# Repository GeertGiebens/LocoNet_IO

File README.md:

# LocoNet_IO

This LocoNet project has moved to this link: [DIY LocoNet S88 DCC](https://github.com/GeertGiebens/DIY_LocoNet_S88_DCC/)

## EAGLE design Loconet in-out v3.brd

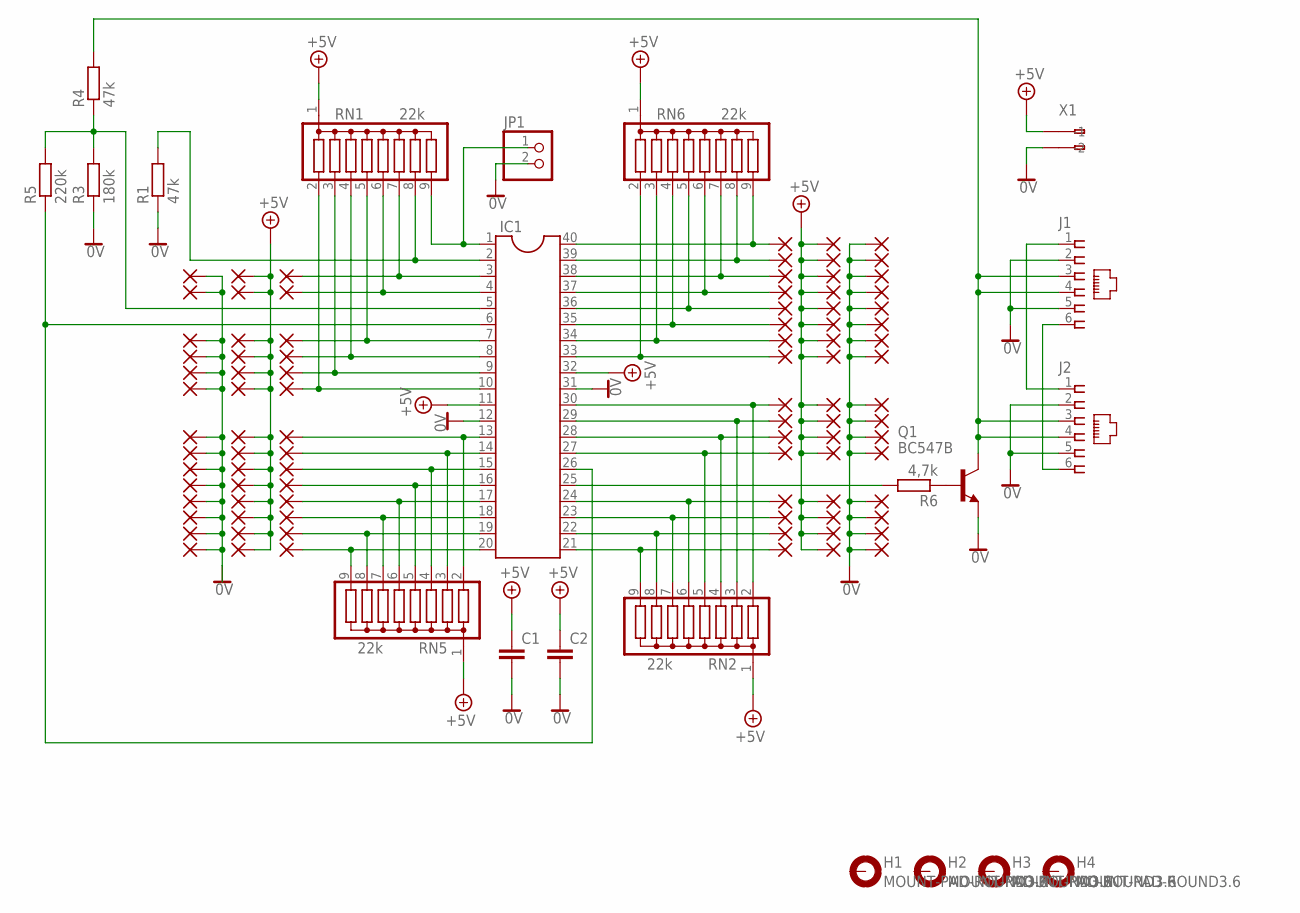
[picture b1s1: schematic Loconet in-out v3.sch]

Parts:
0, 2, 3, 4, 5, 6, 7, 8, 9, 10, 11, 12, 13, 14, 15, 16, 17, 18, 19, 20, 21, 22, 23, 24, 25, 26, 27, 28, 29, 30: 2,15/1,0
1: 1; 2,15/1,0
C1, C2: C-EU025-024X044; C025-024X044
H1, H2, H3, H4: MOUNT-PAD-ROUND3.6; 3,6-PAD
IC1: DIL40
J1, J2: 520250-3
JP1: PINHD-1X2; 1X02
PAD1, PAD2, PAD3, PAD4, PAD5, PAD6, PAD7, PAD8, PAD9, PAD10, PAD11, PAD12, PAD13, PAD14, PAD15, PAD16, PAD17, PAD18, PAD19, PAD20, PAD21, PAD22, PAD23, PAD24, PAD25, PAD26, PAD27, PAD28, PAD29, PAD30, PAD33, PAD35, PAD37, PAD39, PAD41, PAD43, PAD52, PAD53, PAD54, PAD55, PAD56, PAD57, PAD58, PAD59, PAD60, PAD61, PAD62, PAD63, PAD64, PAD65, PAD66, PAD67, PAD68, PAD69, PAD70, PAD71, PAD72, PAD73, PAD74: 2,15/1,0
Q1: BC547B; TO92
R1, R4: 47k; 0204/7
R3: 180k; 0204/7
R5: 220k; 0204/7
R6: 4,7k; 0204/7
RN1, RN2, RN5, RN6: 22k; SIL9
X1: 233-102

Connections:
+5V: 0.1, C1.1, C2.1, IC1.11, IC1.32, PAD33.1, PAD35.1, PAD37.1, PAD39.1, PAD41.1, PAD43.1, PAD52.1, PAD53.1, PAD54.1, PAD55.1, PAD56.1, PAD57.1, PAD58.1, PAD59.1, PAD60.1, PAD61.1, PAD62.1, PAD63.1, PAD64.1, PAD65.1, PAD66.1, PAD67.1, PAD68.1, PAD69.1, PAD70.1, PAD71.1, PAD72.1, PAD73.1, PAD74.1, RN1.1, RN2.1, RN5.1, RN6.1, X1.A1 (-1)
LN_RECEIVER: IC1.6, IC1.26, R5.1
LOCONET: J1.3, J1.4, J2.3, J2.4, Q1.3 (C), R4.2
unnamed: IC1.2, R1.2, RN1.8
unnamed: IC1.5, R3.2, R4.1, R5.2
unnamed: IC1.23, PAD20.1, RN2.7
unnamed: Q1.2 (B), R6.1
unnamed: J1.1, J2.1
unnamed: IC1.1, JP1.1, RN1.9
unnamed: IC1.40, PAD7.1, RN6.9
unnamed: J1.6, J2.6
unnamed: IC1.39, PAD8.1, RN6.8
unnamed: IC1.3, PAD1.1, RN1.7
unnamed: IC1.4, PAD2.1, RN1.6
unnamed: IC1.10, PAD6.1, RN1.2
unnamed: IC1.9, PAD5.1, RN1.3
unnamed: IC1.8, PAD4.1, RN1.4
unnamed: IC1.7, PAD3.1, RN1.5
unnamed: IC1.33, PAD14.1, RN6.2
unnamed: IC1.34, PAD13.1, RN6.3
unnamed: IC1.35, PAD12.1, RN6.4
unnamed: IC1.36, PAD11.1, RN6.5
unnamed: IC1.37, PAD10.1, RN6.6
unnamed: IC1.38, PAD9.1, RN6.7
unnamed: IC1.21, PAD22.1, RN2.9
unnamed: IC1.22, PAD21.1, RN2.8
unnamed: IC1.24, PAD19.1, RN2.6
unnamed: IC1.27, PAD18.1, RN2.5
unnamed: IC1.28, PAD17.1, RN2.4
unnamed: IC1.29, PAD16.1, RN2.3
unnamed: IC1.30, PAD15.1, RN2.2
unnamed: IC1.20, PAD23.1, RN5.9
unnamed: IC1.19, PAD24.1, RN5.8
unnamed: IC1.18, PAD25.1, RN5.7
unnamed: IC1.17, PAD26.1, RN5.6
unnamed: IC1.16, PAD27.1, RN5.5
unnamed: IC1.15, PAD28.1, RN5.4
unnamed: IC1.14, PAD29.1, RN5.3
unnamed: IC1.13, PAD30.1, RN5.2
unnamed: IC1.25, R6.2
unnamed: 1.1, 2.1, 3.1, 4.1, 5.1, 6.1, 7.1, 8.1, 9.1, 10.1, 11.1, 12.1, 13.1, 14.1, 15.1, 16.1, 17.1, 18.1, 19.1, 20.1, 21.1, 22.1, 23.1, 24.1, 25.1, 26.1, 27.1, 28.1, 29.1, 30.1, C1.2, C2.2, IC1.12, IC1.31, J1.2, J1.5, J2.2, J2.5, JP1.2, Q1.1 (E), R1.1, R3.1, X1.A2 (-2)

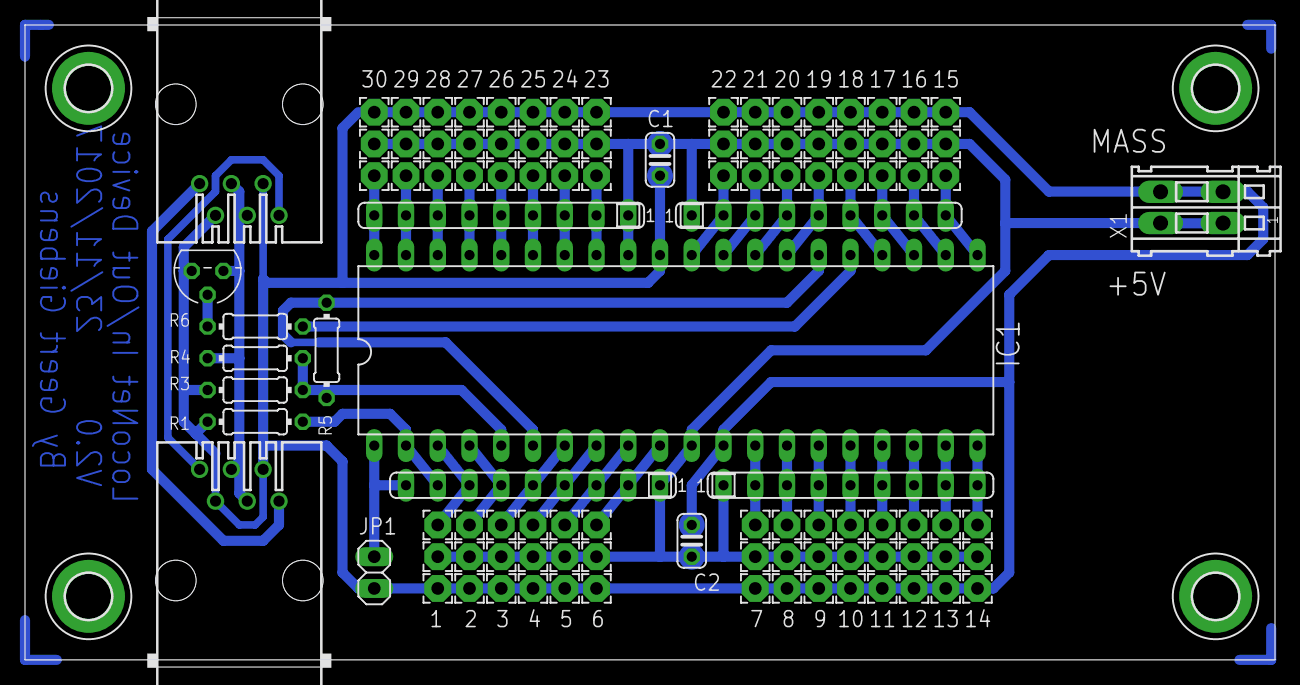
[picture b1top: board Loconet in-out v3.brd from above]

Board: 2 copper layers, 100.0 x 50.8 mm, 111 parts (0 on the bottom side), 41 nets.

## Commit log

2018-01-23 Create README.md
    LocoNet In/Out Device with PIC microcontroller
2018-02-13 Create test
